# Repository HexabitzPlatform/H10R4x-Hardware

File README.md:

# H10R4x-Hardware
Hexabitz Thumb Joystick Module Hardware Design

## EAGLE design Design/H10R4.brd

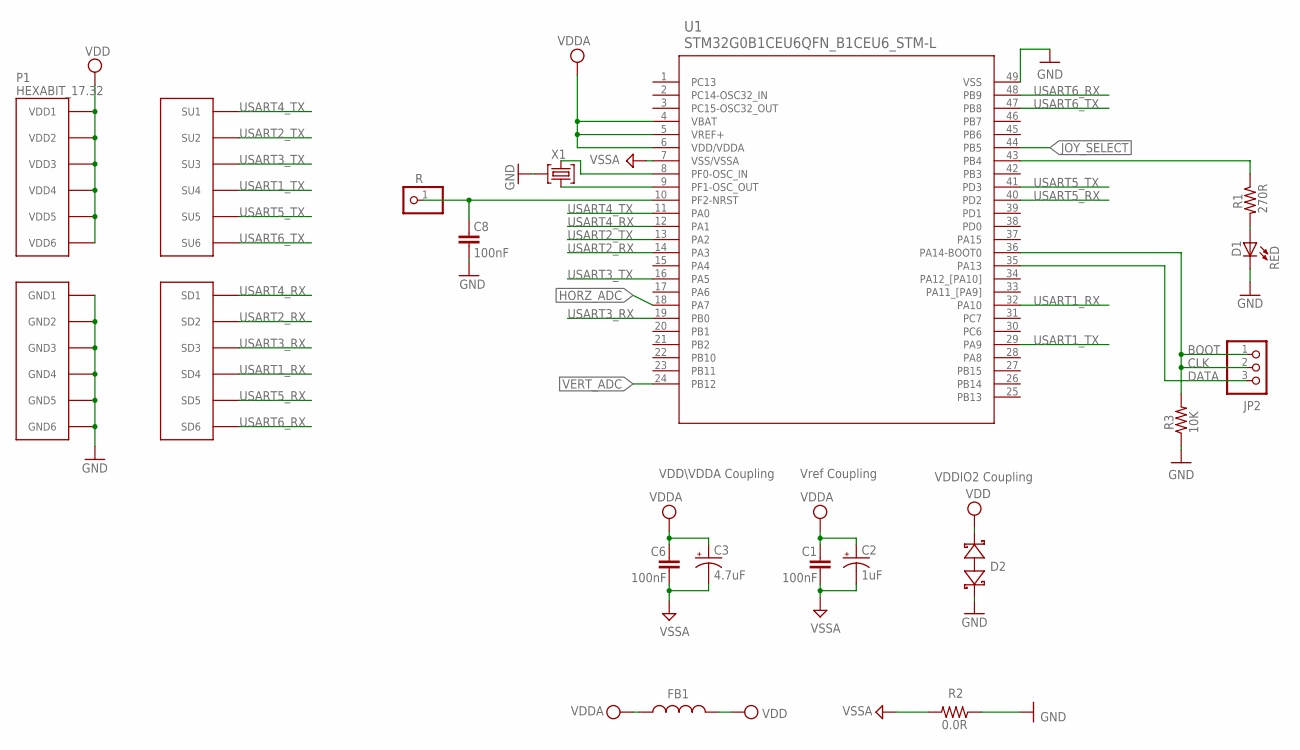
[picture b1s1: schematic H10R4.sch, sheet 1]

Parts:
C1, C6, C8: 100nF; C-0603
C2: 1uF; C-0805-POL
C3: 4.7uF; C-0805-POL
D1: RED; VLMS1300-GS08; MPN VLMS1300-GS08
D2: BOURNS_CDSOD323-T03SCBOURNS_CDSOD323-T03SC_0_0; BOURNS_CDSOD323-T03SC_0
FB1: FB-TDK_MMZ1608Y300B; MPN MMZ1608Y300B
JP2: PINHD-1X3; 1X03
P1: HEXABIT_17.32
R: R; 1X01
R1: 270R; R-0603
R2: 0.0R; R-0603; MPN RC0603JR-070RL
R3: 10K; R-0603
TRIMBLE-LOGO1: HEXA-LOGO
U1: STM32G0B1CEU6QFN_B1CEU6_STM-L; QFN_B1CEU6_STM-L
X1: XTALL_CSTCE8M00G52

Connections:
CLK: JP2.1, JP2.2, R3.2, U1.36 (PA14-BOOT0)
DATA: JP2.3, U1.35 (PA13)
GND: C8.2, D1.C, D2.1 (A), P1.PAD_PD7 (GND1), P1.PAD_PD8 (GND2), P1.PAD_PD9 (GND3), P1.PAD_PD10 (GND4), P1.PAD_PD11 (GND5), P1.PAD_PD12 (GND6), R2.1, R3.1, U1.49 (VSS), X1.P$2 (2); also elsewhere on the board
HORZ_ADC: U1.18 (PA7); also elsewhere on the board
JOY_SELECT: U1.44 (PB5); also elsewhere on the board
unnamed: R1.1, U1.43 (PB4)
unnamed: D1.A, R1.2
unnamed: C8.1, R.1, U1.10 (PF2-NRST)
unnamed: U1.9 (PF1-OSC_OUT), X1.P$1 (1)
unnamed: U1.8 (PF0-OSC_IN), X1.P$3 (3)
USART1_RX: P1.PAD_PD4 (SD4), U1.32 (PA10)
USART1_TX: P1.PAD_PU4 (SU4), U1.29 (PA9)
USART2_RX: P1.PAD_PD2 (SD2), U1.14 (PA3)
USART2_TX: P1.PAD_PU2 (SU2), U1.13 (PA2)
USART3_RX: P1.PAD_PD3 (SD3), U1.19 (PB0)
USART3_TX: P1.PAD_PU3 (SU3), U1.16 (PA5)
USART4_RX: P1.PAD_PD1 (SD1), U1.12 (PA1)
USART4_TX: P1.PAD_PU1 (SU1), U1.11 (PA0)
USART5_RX: P1.PAD_PD5 (SD5), U1.40 (PD2)
USART5_TX: P1.PAD_PU5 (SU5), U1.41 (PD3)
USART6_RX: P1.PAD_PD6 (SD6), U1.48 (PB9)
USART6_TX: P1.PAD_PU6 (SU6), U1.47 (PB8)
VDD: D2.2 (C), FB1.2, P1.PAD_PU7 (VDD1), P1.PAD_PU8 (VDD2), P1.PAD_PU9 (VDD3), P1.PAD_PU10 (VDD4), P1.PAD_PU11 (VDD5), P1.PAD_PU12 (VDD6); also elsewhere on the board
VDDA: C1.1, C2.1 (+), C3.1 (+), C6.1, FB1.1, U1.4 (VBAT), U1.5 (VREF+), U1.6 (VDD/VDDA)
VERT_ADC: U1.24 (PB12); also elsewhere on the board
VSSA: C1.2, C2.2 (-), C3.2 (-), C6.2, R2.2, U1.7 (VSS/VSSA)

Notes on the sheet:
Vref Coupling
VDDIO2 Coupling
VDD\VDDA Coupling
BOOT

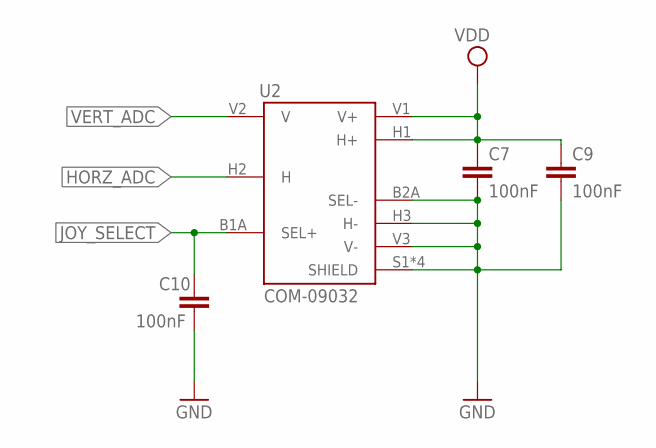
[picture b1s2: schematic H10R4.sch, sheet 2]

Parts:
C7, C10: 100nF; C-0603; TOLERANCE 10%; VOLTAGE_RATING 10V; MPN C0603C104K8RACTU
C9: 100nF; C-0603
U2: COM-09032; XDCR_COM-09032

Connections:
GND: C7.2, C9.2, C10.2, U2.B2A (SEL-), U2.H3 (H-), U2.S1 (SHIELD), U2.S2 (SHIELD), U2.S3 (SHIELD), U2.S4 (SHIELD), U2.V3 (V-); also elsewhere on the board
HORZ_ADC: U2.H2 (H); also elsewhere on the board
JOY_SELECT: C10.1, U2.B1A (SEL+); also elsewhere on the board
VDD: C7.1, C9.1, U2.H1 (H+), U2.V1 (V+); also elsewhere on the board
VERT_ADC: U2.V2 (V); also elsewhere on the board

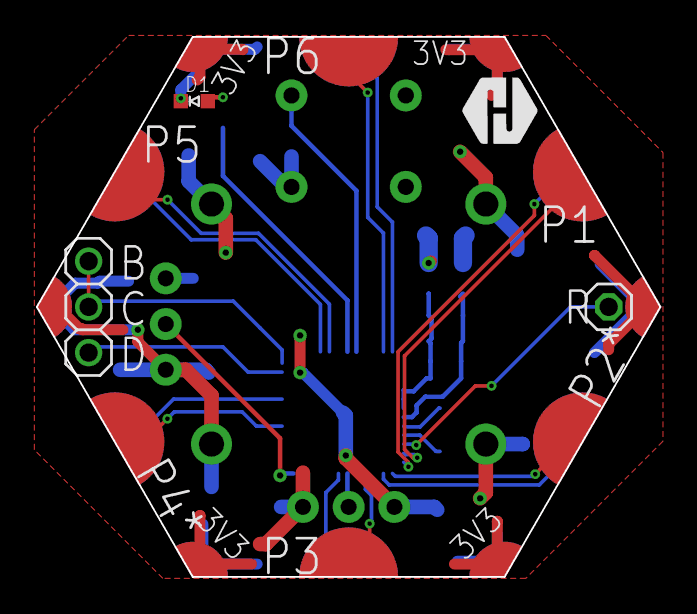
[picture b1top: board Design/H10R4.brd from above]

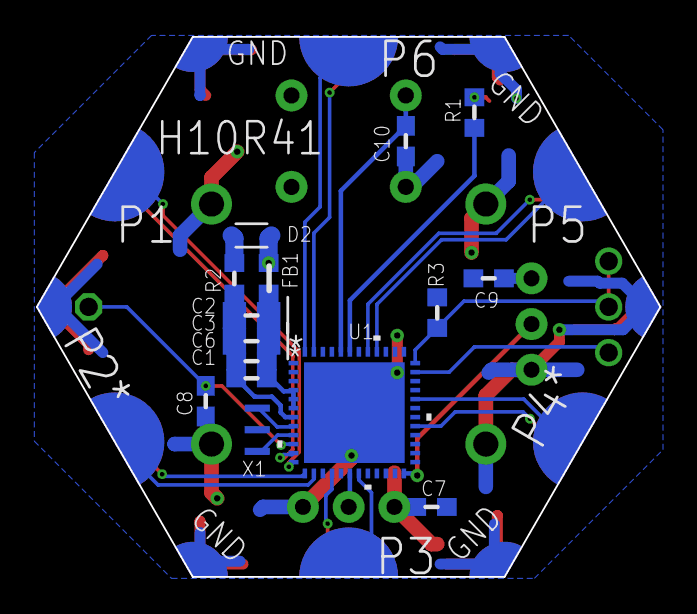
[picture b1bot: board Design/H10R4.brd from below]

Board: 2 copper layers, 34.6 x 30.0 mm, 21 parts (15 on the bottom side), 26 nets.

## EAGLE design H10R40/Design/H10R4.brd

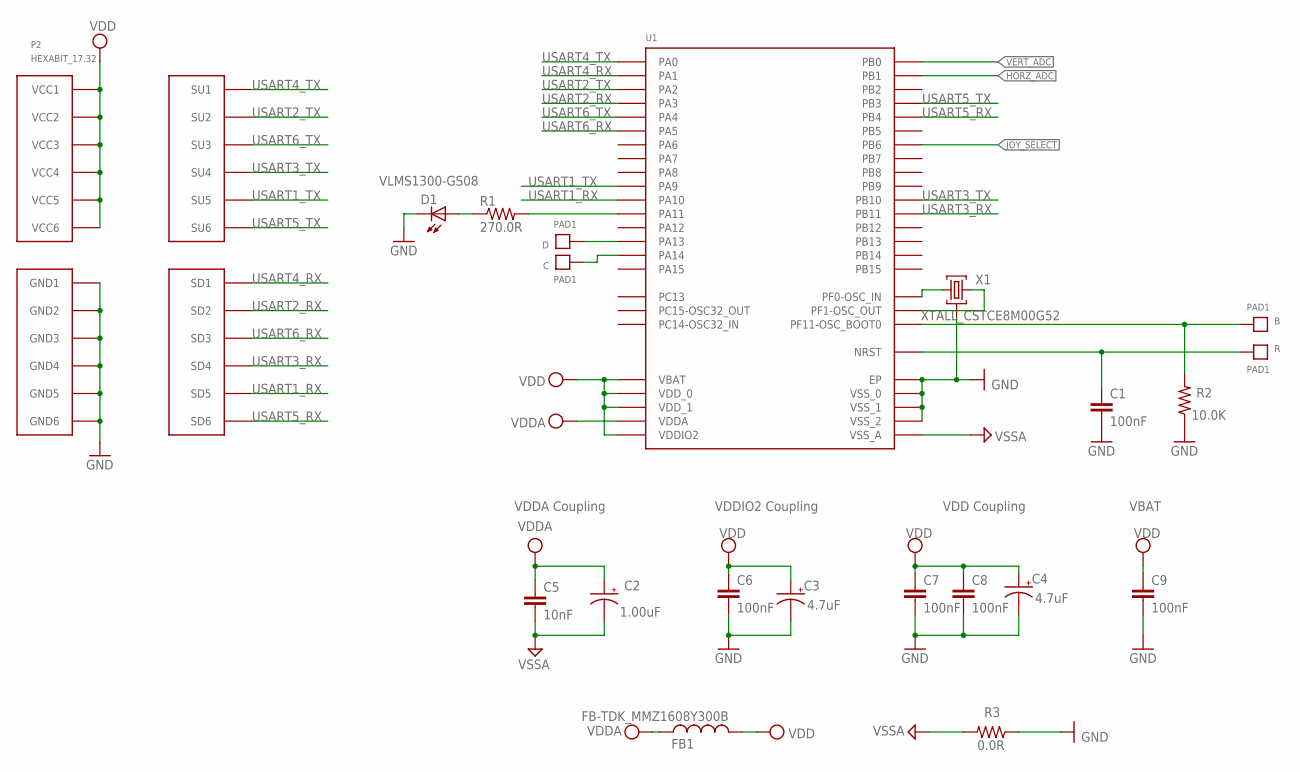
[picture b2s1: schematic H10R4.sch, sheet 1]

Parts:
B: PAD1
C: PAD1
C1, C6, C8: 100nF; C-0603; TOLERANCE 10%; VOLTAGE_RATING 10V; MPN C0603C104K8RACTU
C2: 1.00uF; C-0805-POL; TOLERANCE 10%; VOLTAGE_RATING 16V; MPN CC0805KKX7R7BB105
C3, C4: 4.7uF; C-0805-POL; TOLERANCE 10%; VOLTAGE_RATING 25V; MPN GRM21BC81E475KA12L
C5: 10nF; C-0603; TOLERANCE 10%; VOLTAGE_RATING 50V; MPN C0603C103K5RACTU
C7: 100nF; C-0603; TOLERANCE 10%; VOLTAGE_RATING 10; MPN C0603C104K8RACTU
C9: 100nF; C-0603; TOLERANCE 10V; VOLTAGE_RATING 10%; MPN C0603C104K8RACTU
D: PAD1
D1: VLMS1300-GS08; MPN VLMS1300-GS08
FB1: FB-TDK_MMZ1608Y300B; MPN MMZ1608Y300B
P2: HEXABIT_17.32
R: PAD1
R1: 270.0R; R-0603; TOLERANCE 1%; MPN RC0603FR-07270RL
R2: 10.0K; R-0603; TOLERANCE 5%; MPN RC0603JR-0710KL
R3: 0.0R; R-0603; MPN RC0603JR-070RL
U1: STM32F091CBU6
X1: XTALL_CSTCE8M00G52

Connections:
B: B.P$1, B.P$2, R2.2, U1.P$44 (PF11-OSC_BOOT0)
GND: C1.2, C3.2 (-), C4.2 (-), C6.2, C7.2, C8.2, C9.2, D1.C, P2.7 (GND1), P2.8 (GND2), P2.9 (GND3), P2.10 (GND4), P2.11 (GND5), P2.12 (GND6), R2.1, R3.1, U1.EP, U1.P$23 (VSS_0), U1.P$35 (VSS_1), U1.P$47 (VSS_2), X1.P$2 (2); also elsewhere on the board
HORZ_ADC: U1.P$19 (PB1); also elsewhere on the board
JOY_SELECT: U1.P$42 (PB6); also elsewhere on the board
unnamed: D.P$1, D.P$2, U1.P$34 (PA13)
unnamed: C.P$1, C.P$2, U1.P$37 (PA14)
unnamed: R1.2, U1.P$32 (PA11)
unnamed: D1.A, R1.1
unnamed: U1.P$5 (PF0-OSC_IN), X1.P$1 (1)
unnamed: U1.P$6 (PF1-OSC_OUT), X1.P$3 (3)
R: C1.1, R.P$1, R.P$2, U1.P$7 (NRST)
USART1_RX: P2.23 (SD5), U1.P$31 (PA10)
USART1_TX: P2.17 (SU5), U1.P$30 (PA9)
USART2_RX: P2.20 (SD2), U1.P$13 (PA3)
USART2_TX: P2.14 (SU2), U1.P$12 (PA2)
USART3_RX: P2.22 (SD4), U1.P$22 (PB11)
USART3_TX: P2.16 (SU4), U1.P$21 (PB10)
USART4_RX: P2.19 (SD1), U1.P$11 (PA1)
USART4_TX: P2.13 (SU1), U1.P$10 (PA0)
USART5_RX: P2.25 (SD6), U1.P$40 (PB4)
USART5_TX: P2.18 (SU6), U1.P$39 (PB3)
USART6_RX: P2.21 (SD3), U1.P$15 (PA5)
USART6_TX: P2.15 (SU3), U1.P$14 (PA4)
VDD: C3.1 (+), C4.1 (+), C6.1, C7.1, C8.1, C9.1, FB1.2, P2.1 (VCC1), P2.2 (VCC2), P2.3 (VCC3), P2.4 (VCC4), P2.5 (VCC5), P2.6 (VCC6), U1.P$1 (VBAT), U1.P$24 (VDD_0), U1.P$36 (VDDIO2), U1.P$48 (VDD_1)
VDDA: C2.1 (+), C5.1, FB1.1, U1.P$9 (VDDA); also elsewhere on the board
VERT_ADC: U1.P$18 (PB0); also elsewhere on the board
VSSA: C2.2 (-), C5.2, R3.2, U1.P$8 (VSS_A); also elsewhere on the board

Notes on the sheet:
VDDA Coupling
VDDIO2 Coupling
VDD Coupling
VBAT

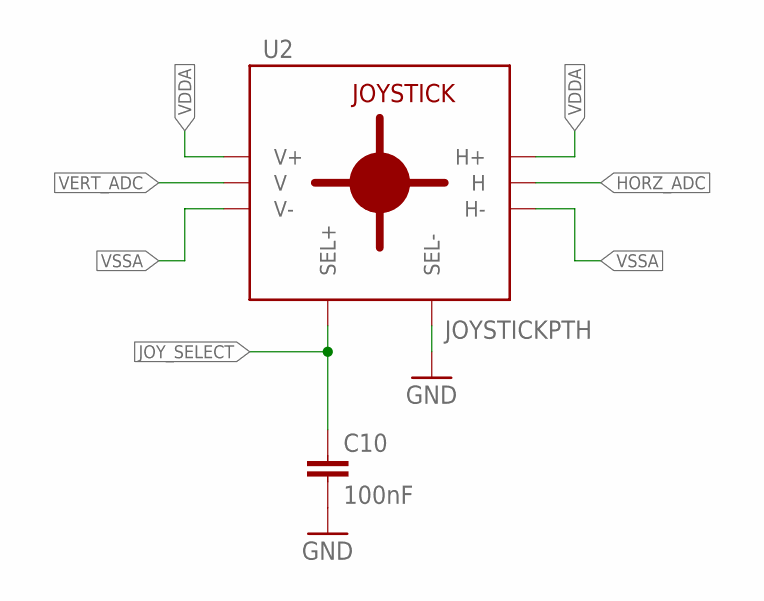
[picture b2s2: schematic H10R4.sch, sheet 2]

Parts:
C10: 100nF; C-0603; TOLERANCE 10%; VOLTAGE_RATING 10V; MPN C0603C104K8RACTU
U2: JOYSTICKPTH; JOYSTICK

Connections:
GND: C10.2, U2.B2A (SEL-); also elsewhere on the board
HORZ_ADC: U2.H2 (H); also elsewhere on the board
JOY_SELECT: C10.1, U2.B1A (SEL+); also elsewhere on the board
VDDA: U2.H1 (H+), U2.V1 (V+); also elsewhere on the board
VERT_ADC: U2.V2 (V); also elsewhere on the board
VSSA: U2.H3 (H-), U2.V3 (V-); also elsewhere on the board

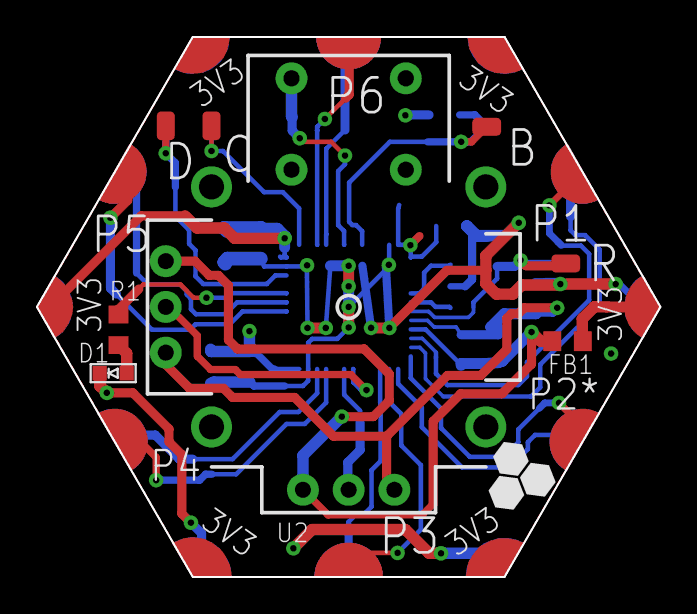
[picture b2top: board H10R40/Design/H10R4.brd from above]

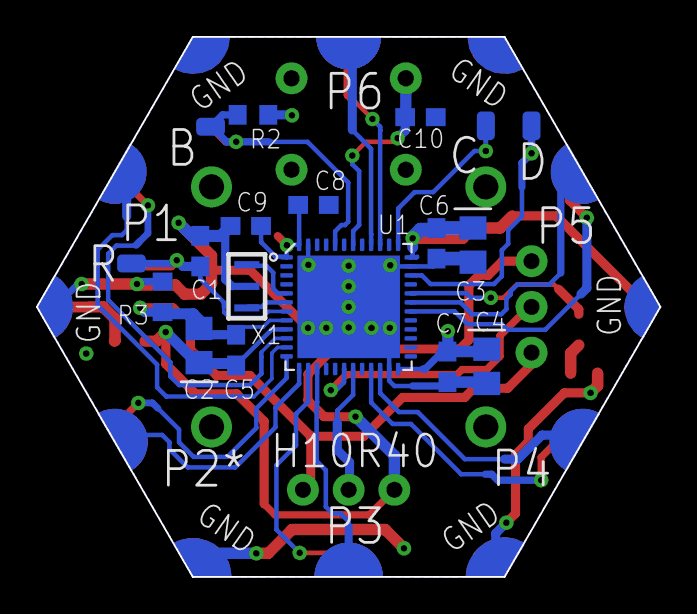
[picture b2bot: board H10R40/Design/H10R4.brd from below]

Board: 2 copper layers, 34.6 x 30.0 mm, 23 parts (14 on the bottom side), 27 nets.

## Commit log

2019-05-23 First release rev 0
2019-08-06 Update H10R4.xlsx
    Updating BOM
2019-08-08 Update H10R4.pdf
    Updated schematics to fix colors
2025-01-26 -Add TVS diode -Change the MCU to STM32G0B1CEU6 -Activate the thermal option for the polygon -Improve the layout design for better performance

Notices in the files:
parts and their libraries:
COPYRIGHT: Copyright (C) 2021 Ultra Librarian. All rights reserved.
